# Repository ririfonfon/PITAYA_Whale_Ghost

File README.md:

# WHALE GHOST
http://www.pitaya.fr/projet//whale-ghost/p3c2pr70.html

## Arduino ESP32

L'iD et le NODE_SUBNET sont enregistrés dans la mémoire Flash.
Pour les changer il faut décommeneter les #define correspondant.

Si le SUBNET est à 0, l'ESP32 se connectera au wifi "whale" sans mot de passe (ssid défini dans wifi.ino)
Son IP sera 192.168.0.(100+ID)
Le Server devra avoir l'IP 192.168.0.200

Si le SUBNET est > 0, par exemple 2, l'ESP32 se connectera au wifi "whale2" sans mot de passe
Son IP sera 192.168.2.(100+ID)
Le Server devra avoir l'IP 192.168.2.200  

## Antenne

Config Ubiquity:

- Onglet UBNT (le 1er) : 
    - airMAX : DISABLE
    
- Onglet Wireless:
    - Wireless Mode: Access Point
    - SSID: whale (SUBNET 0) // whale1 (SUBNET 1) // whale2 (SUBNET 2)
    - Channel Width: 20Mhz
    - Frequency: à choisir en fonction du lieu (par exemple 2437)
                        ecarter chaque subnet d'au moins 3 frequences.
                        attention: ne pas utiliser la dernière fréquence: elle est incompatible avec ESP32 !!
                        ne pas choisir auto, qui risque d'utiliser la dernière fréquence incompatible avec ESP32 !!
    
    - Output Power: à fond ?
    - Data Rate Module: Default
    - Max TX Rate, Mbps: MCS 15 / auto
    - Security: none
    - RADIUS MAC: disable
    - MAC ACL: disable
    
- Onglet Network:
    - Network Mode: Bridge
    - Disable Network: None
    - Config Mode: Simple
    - Management: Static
    - IP Address: 192.168.SUBNET.20     (SUBNET is 0, 1 or 2)
    - Netmask: 255.255.255.0
    - Gateway IP: 192.168.SUBNET.1
    
- Onglet Advanced:
    - RTS Threshold: 2346 / Off
    - Distance: Auto Adjust
    - Aggregation: DISABLE
    - Multicast Data: Allow
    - Multicast Enhancement: Enable
    - Installer EIRP Control: Disable
    - Extra Reporting: Enable
    - Client Isolation: Disable
    - Sensitivity Threshold, dBm: Off

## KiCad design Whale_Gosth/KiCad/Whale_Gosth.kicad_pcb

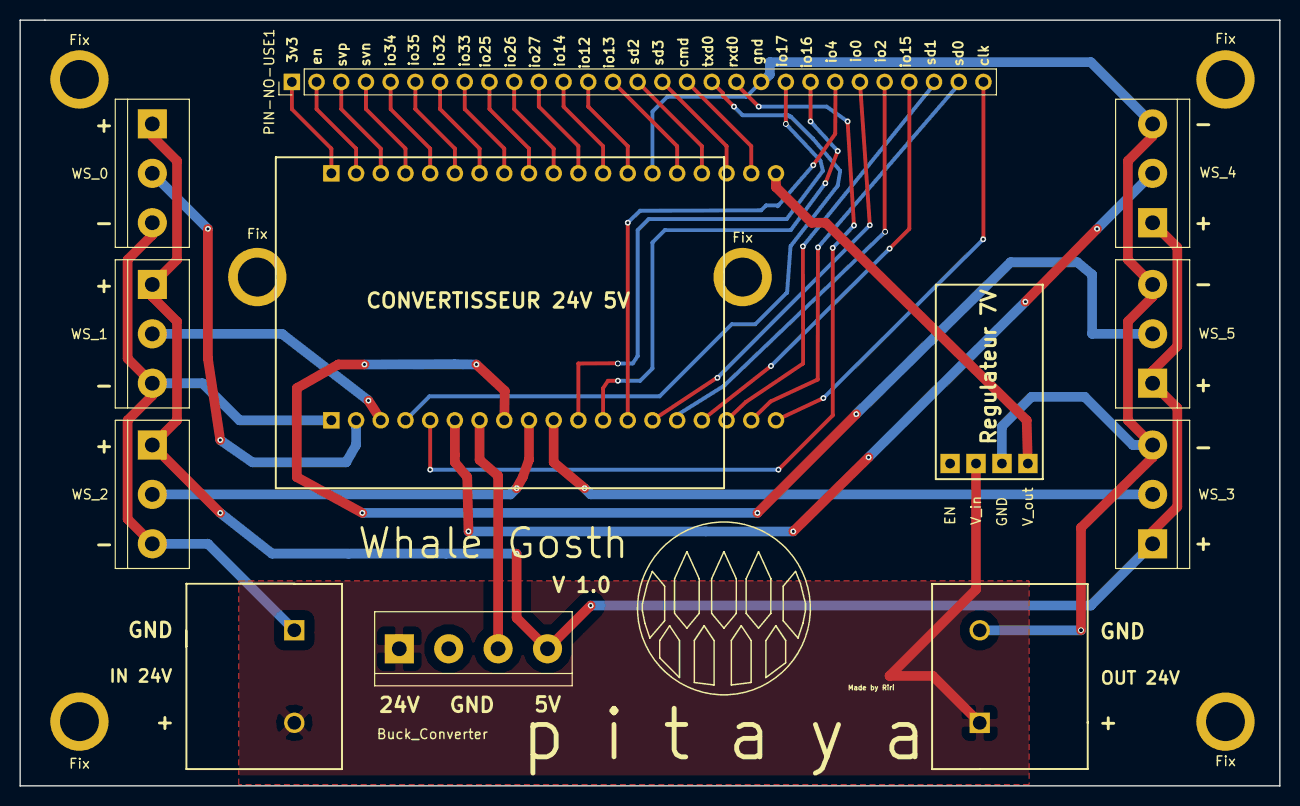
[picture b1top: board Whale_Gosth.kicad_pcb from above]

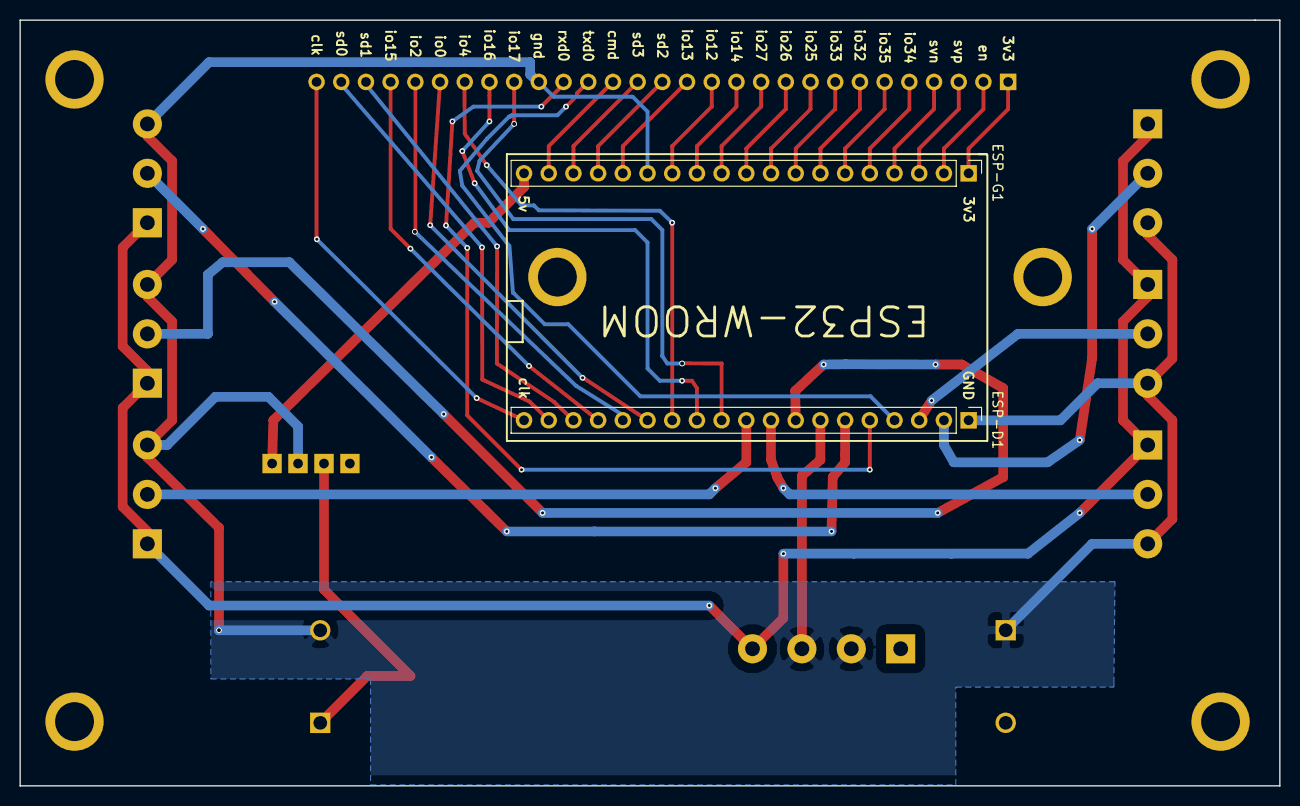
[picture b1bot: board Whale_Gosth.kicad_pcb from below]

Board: 2 copper layers, 129.5 x 78.7 mm, 22 parts (2 on the bottom side), 38 nets.

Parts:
Buck_Converter: TerminalBlock_bornier-4_P5.08mm
EN: SolderWirePad_single_2mmDrill
ESP-D1: ESP32-D; Socket_Strip_Straight_1x19_Pitch2.54mm
ESP-G1: ESP32-G; Socket_Strip_Straight_1x19_Pitch2.54mm
Fix: Fix; SolderWirePad_single_2mmDrill
Fix#2, Fix#3, Fix#4, Fix#5, Fix#6: Fix; SolderWirePad_single_2mmDrill
GND: SolderWirePad_single_2mmDrill
IN 24V: 1902547; SHDR2W120P0X952_1X2_1904X1600X2150P
OUT 24V: 1902547; SHDR2W120P0X952_1X2_1904X1600X2150P
PIN-NO-USE1: PIN-NO-USE; Socket_Strip_Straight_1x29_Pitch2.54mm
V_in: SolderWirePad_single_2mmDrill
V_out: SolderWirePad_single_2mmDrill
WS_0, WS_1, WS_2, WS_3, WS_4, WS_5: TerminalBlock_bornier-3_P5.08mm

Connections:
3V3: ESP-G1.1, PIN-NO-USE1.1
+24V: Buck_Converter.1, IN 24V.2, OUT 24V.1, V_in.1
CLK: ESP-D1.19, PIN-NO-USE1.29
CMD: ESP-G1.18, PIN-NO-USE1.17
EN: ESP-G1.2, PIN-NO-USE1.2
GND: Buck_Converter.2, Buck_Converter.3, ESP-D1.1, ESP-D1.7, ESP-G1.14, GND.1, IN 24V.1, OUT 24V.2, PIN-NO-USE1.20, WS_0.3, WS_1.3, WS_2.3, WS_3.3, WS_4.3, WS_5.3
IO0: ESP-D1.14, PIN-NO-USE1.24
IO2: ESP-D1.15, PIN-NO-USE1.25
IO4: ESP-D1.13, PIN-NO-USE1.23
IO12: ESP-G1.13, PIN-NO-USE1.13
IO13: ESP-G1.15, PIN-NO-USE1.14
IO14: ESP-G1.12, PIN-NO-USE1.12
IO15: ESP-D1.16, PIN-NO-USE1.26
IO16: ESP-D1.12, PIN-NO-USE1.22
IO17: ESP-D1.11, PIN-NO-USE1.21
IO25: ESP-G1.9, PIN-NO-USE1.9
IO26: ESP-G1.10, PIN-NO-USE1.10
IO27: ESP-G1.11, PIN-NO-USE1.11
IO32: ESP-G1.7, PIN-NO-USE1.7
IO33: ESP-G1.8, PIN-NO-USE1.8
IO34: ESP-G1.5, PIN-NO-USE1.5
IO35: ESP-G1.6, PIN-NO-USE1.6
unnamed: Buck_Converter.4, WS_0.1, WS_1.1, WS_2.1, WS_3.1, WS_4.1, WS_5.1
unnamed: ESP-G1.19, V_out.1
RXD0: ESP-D1.5, PIN-NO-USE1.19
SD0: ESP-D1.18, PIN-NO-USE1.28
SD1: ESP-D1.17, PIN-NO-USE1.27
SD2: ESP-G1.16, PIN-NO-USE1.15
SD3: ESP-G1.17, PIN-NO-USE1.16
SVN: ESP-G1.4, PIN-NO-USE1.4
SVP: ESP-G1.3, PIN-NO-USE1.3
TXDO: ESP-D1.4, PIN-NO-USE1.18
WS0: ESP-D1.2, WS_0.2
WS1: ESP-D1.3, WS_1.2
WS2: ESP-D1.9, WS_2.2
WS3: ESP-D1.10, WS_3.2
WS4: ESP-D1.6, WS_4.2
WS5: ESP-D1.8, WS_5.2

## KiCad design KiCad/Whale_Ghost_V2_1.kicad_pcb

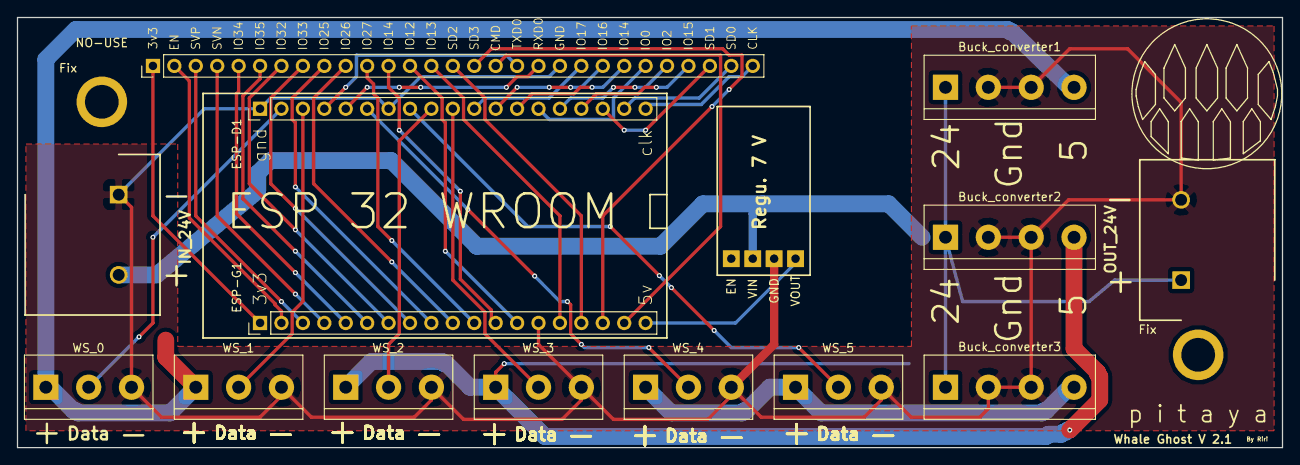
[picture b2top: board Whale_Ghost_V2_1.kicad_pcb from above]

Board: 2 copper layers, 150.0 x 51.0 mm, 20 parts (0 on the bottom side), 40 nets.

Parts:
Buck_converter1: BUCK-CONVERTER1; TerminalBlock_bornier-4_P5.08mm
Buck_converter2: BUCK-CONVERTER2; TerminalBlock_bornier-4_P5.08mm
Buck_converter3: BUCK-CONVERTER3; TerminalBlock_bornier-4_P5.08mm
EN: SolderWirePad_single_2mmDrill
ESP-D1: ESP32-D; Socket_Strip_Straight_1x19_Pitch2.54mm
ESP-G1: ESP32-G; Socket_Strip_Straight_1x19_Pitch2.54mm
Fix: SolderWirePad_single_2-5mmDrill
Fix#2: SolderWirePad_single_2-5mmDrill
GND: SolderWirePad_single_2mmDrill
IN_24V: SHDR2W120P0X952_1X2_1904X1600X2150P
NO-USE: PIN-NO-USE; Socket_Strip_Straight_1x29_Pitch2.54mm
OUT_24V: SHDR2W120P0X952_1X2_1904X1600X2150P
VIN: SolderWirePad_single_2mmDrill
VOUT: SolderWirePad_single_2mmDrill
WS_0, WS_1, WS_2, WS_3, WS_4, WS_5: Screw_Terminal_1x03; TerminalBlock_bornier-3_P5.08mm

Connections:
3V3: ESP-G1.1, NO-USE.1
+24V: Buck_converter1.1, Buck_converter2.1, Buck_converter3.1, IN_24V.2, OUT_24V.1, VIN.1
CLK: ESP-D1.19, NO-USE.29
CMD: ESP-G1.18, NO-USE.17
EN: ESP-G1.2, NO-USE.2
GND: Buck_converter1.2, Buck_converter1.3, Buck_converter2.2, Buck_converter2.3, Buck_converter3.2, Buck_converter3.3, ESP-D1.1, ESP-D1.7, ESP-G1.14, GND.1, IN_24V.1, NO-USE.20, OUT_24V.2, WS_0.3, WS_1.3, WS_2.3, WS_3.3, WS_4.3, WS_5.3
IO0: ESP-D1.14, NO-USE.24
IO2: ESP-D1.15, NO-USE.25
IO4: ESP-D1.13, NO-USE.23
IO12: ESP-G1.13, NO-USE.13
IO13: ESP-G1.15, NO-USE.14
IO14: ESP-G1.12, NO-USE.12
IO15: ESP-D1.16, NO-USE.26
IO16: ESP-D1.12, NO-USE.22
IO17: ESP-D1.11, NO-USE.21
IO25: ESP-G1.9, NO-USE.9
IO26: ESP-G1.10, NO-USE.10
IO27: ESP-G1.11, NO-USE.11
IO32: ESP-G1.7, NO-USE.7
IO33: ESP-G1.8, NO-USE.8
IO34: ESP-G1.5, NO-USE.5
IO35: ESP-G1.6, NO-USE.6
unnamed: Buck_converter1.4, WS_0.1, WS_1.1
unnamed: Buck_converter2.4, WS_2.1, WS_3.1
unnamed: Buck_converter3.4, WS_4.1, WS_5.1
unnamed: ESP-G1.19, VOUT.1
RXD0: ESP-D1.5, NO-USE.19
SD0: ESP-D1.18, NO-USE.28
SD1: ESP-D1.17, NO-USE.27
SD2: ESP-G1.16, NO-USE.15
SD3: ESP-G1.17, NO-USE.16
SVN: ESP-G1.4, NO-USE.4
SVP: ESP-G1.3, NO-USE.3
TXDO: ESP-D1.4, NO-USE.18
WS0: ESP-D1.2, WS_0.2
WS1: ESP-D1.3, WS_1.2
WS2: ESP-D1.9, WS_2.2
WS3: ESP-D1.10, WS_3.2
WS4: ESP-D1.6, WS_4.2
WS5: ESP-D1.8, WS_5.2

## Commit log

2018-02-01 esp32
    esp_32_6ws
2018-02-02 Change dir name
2018-02-02 change node id
2018-02-02 Readme
2018-02-03 transfert vendredi
2018-02-03 plus
2018-02-03 changer init test led
    for i du numberofled n'est pas utile remplacer par NUM_LEDS_PER_STRIP
    et donc aussi strands[x]->pixels[i-NUM_LEDS_PER_STRIP*x] = ...
    par strands[x]->pixels[i] = pixelFromRGB(TEST_VAL, 0, 0);
2018-02-06 pcb_whale_ghost
    premiere etape , enlever le connecteur reg 5v et le remplacer par son imprainte avec 4 pastilles traversante
2018-02-06 auto reconnect
    rajout de auto reconnect dans la loop
2018-02-06 jpeg
2018-02-06 pcb v1.0
2018-02-06 pcb_cote
2018-02-06 changer impreinte esp de 12 a 11 pas 2.54
2018-02-07 angle droit
2018-02-08 v2.1
2018-02-08 image plus
2018-02-08 ajout du pcb
2018-02-08 inversion de polariter ws
2018-02-12 NodeJS stratum Bridge
2018-02-13 refresh 10
2018-02-14 send esp 1 to 20
2018-03-01 nano station m2
2018-03-01 remove
2018-03-01 Max init
2018-03-01 loop
2018-03-01 OTA esp32
2018-03-01 gitignore
2018-03-01 Remove OTA esp32
2018-03-01 autostart
2018-03-01 Re-OTA with firmware 9512368 (git checkout 9512368) on esp32 arduino hardware
2018-03-01 clean DS_Store
2018-03-01 clean OTA
2018-03-02 Fix WIFI reconnect
2018-03-02 Moved Bridge
2018-03-02 Disable Restart.. infinte retry WIFI
2018-03-02 Disable Debug
2018-03-04 ctrl t
2018-03-06 fps control
2018-03-06 test zlib
2018-03-07 carre led et no restart wifi lose
2018-03-07 Blackout + function square
2018-03-07 Framerate set
2018-03-07 reconection v6
2018-03-07 old firm
2018-03-08 cleanup
2018-03-08 new vid
2018-03-08 Fix reconnect / blackout issues
2018-03-12 Blackout + OTA + reconnect FIX
2018-03-12 essais mini
2018-03-12 big commit
2018-03-12 added dmxusbpro
2018-03-12 stop between 2 loops
2018-03-12 timeline ok
2018-03-12 timeline encore
2018-03-13 keyframe: restart debug
2018-04-07 new son
2018-04-11 grave new 1 etc
2018-04-11 plus correcteur avant le carre
2018-04-13 Modifs pendant montage
    Video:
    - Button broadcast
    - Button 1/2 Baleine
    Winch:
    - No Autostart - No Autostop
2018-04-13 grave
2018-04-13 debug baltimore
    black led en mauve
    wifi.begin(ssid) no pass word
    v11
2018-04-13 test ok
    change mauve en demi blanc pour general press
2018-04-14 Delay audio
2018-04-15 master audio
2018-04-15 new sound
2018-10-11 correction
2018-10-12 new version
2018-10-12 new work
2018-10-13 plus mp3
2018-10-13 multi debug
2018-10-13 changer serial mp3 en 32 tx et 33 rx
2018-10-16 insertion i2c
2018-10-16 essais spi
2018-10-16 esp8266 sr
2018-10-16 lampost version esp 8266 valable
2018-10-16 plus touch marche pas
2018-10-16 naze
2018-10-16 addd
2018-10-20 cmd != *
2018-10-20 new pin ou i2c
2018-10-20 essais i2c
2018-10-20 i2c esp8266
2018-10-20 i2c micro_pro
2018-10-20 i2c_lamp_final
2018-10-20 clean_000
2018-10-20 add variable
2018-10-20 clean
2018-10-20 add I2C_request
2018-10-20 add check_mp3
2018-10-20 add no_presence, presence, temp_mp3, touch_gate, loop_time, et calibration de divers variables
2018-10-20 comment variable
2018-10-20 add m time_loop i2c
2018-10-20 add DEBUG & clean
2018-10-20 add devlopement repertoire
2018-10-20 schema
2018-10-20 add touch
2018-10-20 comment
2018-10-20 change fade time
2018-10-20 loop time fade touch
2018-10-20 debugage de fade pink_red
2018-10-21 add timing de fade white
    il arrive quand le fade whiteest lancer qu il bloc plus longtemps que la normal voire3 a 4 cycles
2018-10-21 add loop time fade white no_presence
2018-10-22 add set volume mp3
2018-11-06 fabric
2018-11-19 hc-sr501
    changement du dectecteur ultra son par un detecteur infra rouge
2018-11-19 oublie =
2018-11-21 calcule de temps d'une cue
2018-11-22 timming
2018-11-28 file
2018-11-28 add fade touch
2018-11-28 add id division par 3 du play integration du /3 dans seq loop
2018-11-29 calibrage chez pitaya
2018-11-30 check
2018-11-30 integration du carre dans le send dmx
2018-11-30 carre moins
2018-11-30 carre
2018-11-30 check r g b
2018-11-30 new capa
2018-11-30 integration dmx_ dans tous le code
2018-11-30 dummy de r v b pour condition
2018-12-01 ver 1 son discour
2018-12-01 codage seq lampa 1 ok
2018-12-01 lampa_1 & 2 & 3 seq ok
2018-12-02 ver fade bingo ok
2018-12-02 new song
2018-12-02 calage de new song
2018-12-03 sd lampa_1
2018-12-03 desactivation du touch
2018-12-03 selection du senario
2018-12-03 affine temp de variable et remise a zero du lecteur
2018-12-03 new sans touch
2018-12-04 lampa3 ok
2018-12-04 calage lampa 1 & 2
2018-12-04 lampa 1&2&3 ok c'est dans la boite
2018-12-05 new_senario
2018-12-05 new scenario 8/12
2019-01-07 no password
2019-01-08 new reseau
2019-01-08 Baltimore
2019-01-08 Fix Merge + ESP v8: SUBNETs
2019-01-08 IP odd or even
2019-01-08 re-sync
2019-01-08 add whale1/whale2 subnet
2019-01-08 blackout
2019-01-08 patch test
2019-01-08 master anim
2019-01-08 Ready to go
2019-01-12 london bug
2019-01-12 subnet id et ssid manuel
2019-01-12 ids london
2019-01-12 offsets winches
2019-01-12 offsetok
2019-01-13 master controller
2019-01-13 english txt
2019-01-13 master ok
2019-01-13 last instructions
2019-01-13 rien
2019-02-01 gravage london
2020-02-06 BXL ready
2021-06-08 Create espdecode
2021-06-28 dossier/
2021-06-28 add nano station
2021-07-04 whale_ghost VsCode platformio
2021-07-04 Create ota
2021-07-04 Create otaupdate
2021-07-05 auto ssid
2021-10-07 add antennes.zip
